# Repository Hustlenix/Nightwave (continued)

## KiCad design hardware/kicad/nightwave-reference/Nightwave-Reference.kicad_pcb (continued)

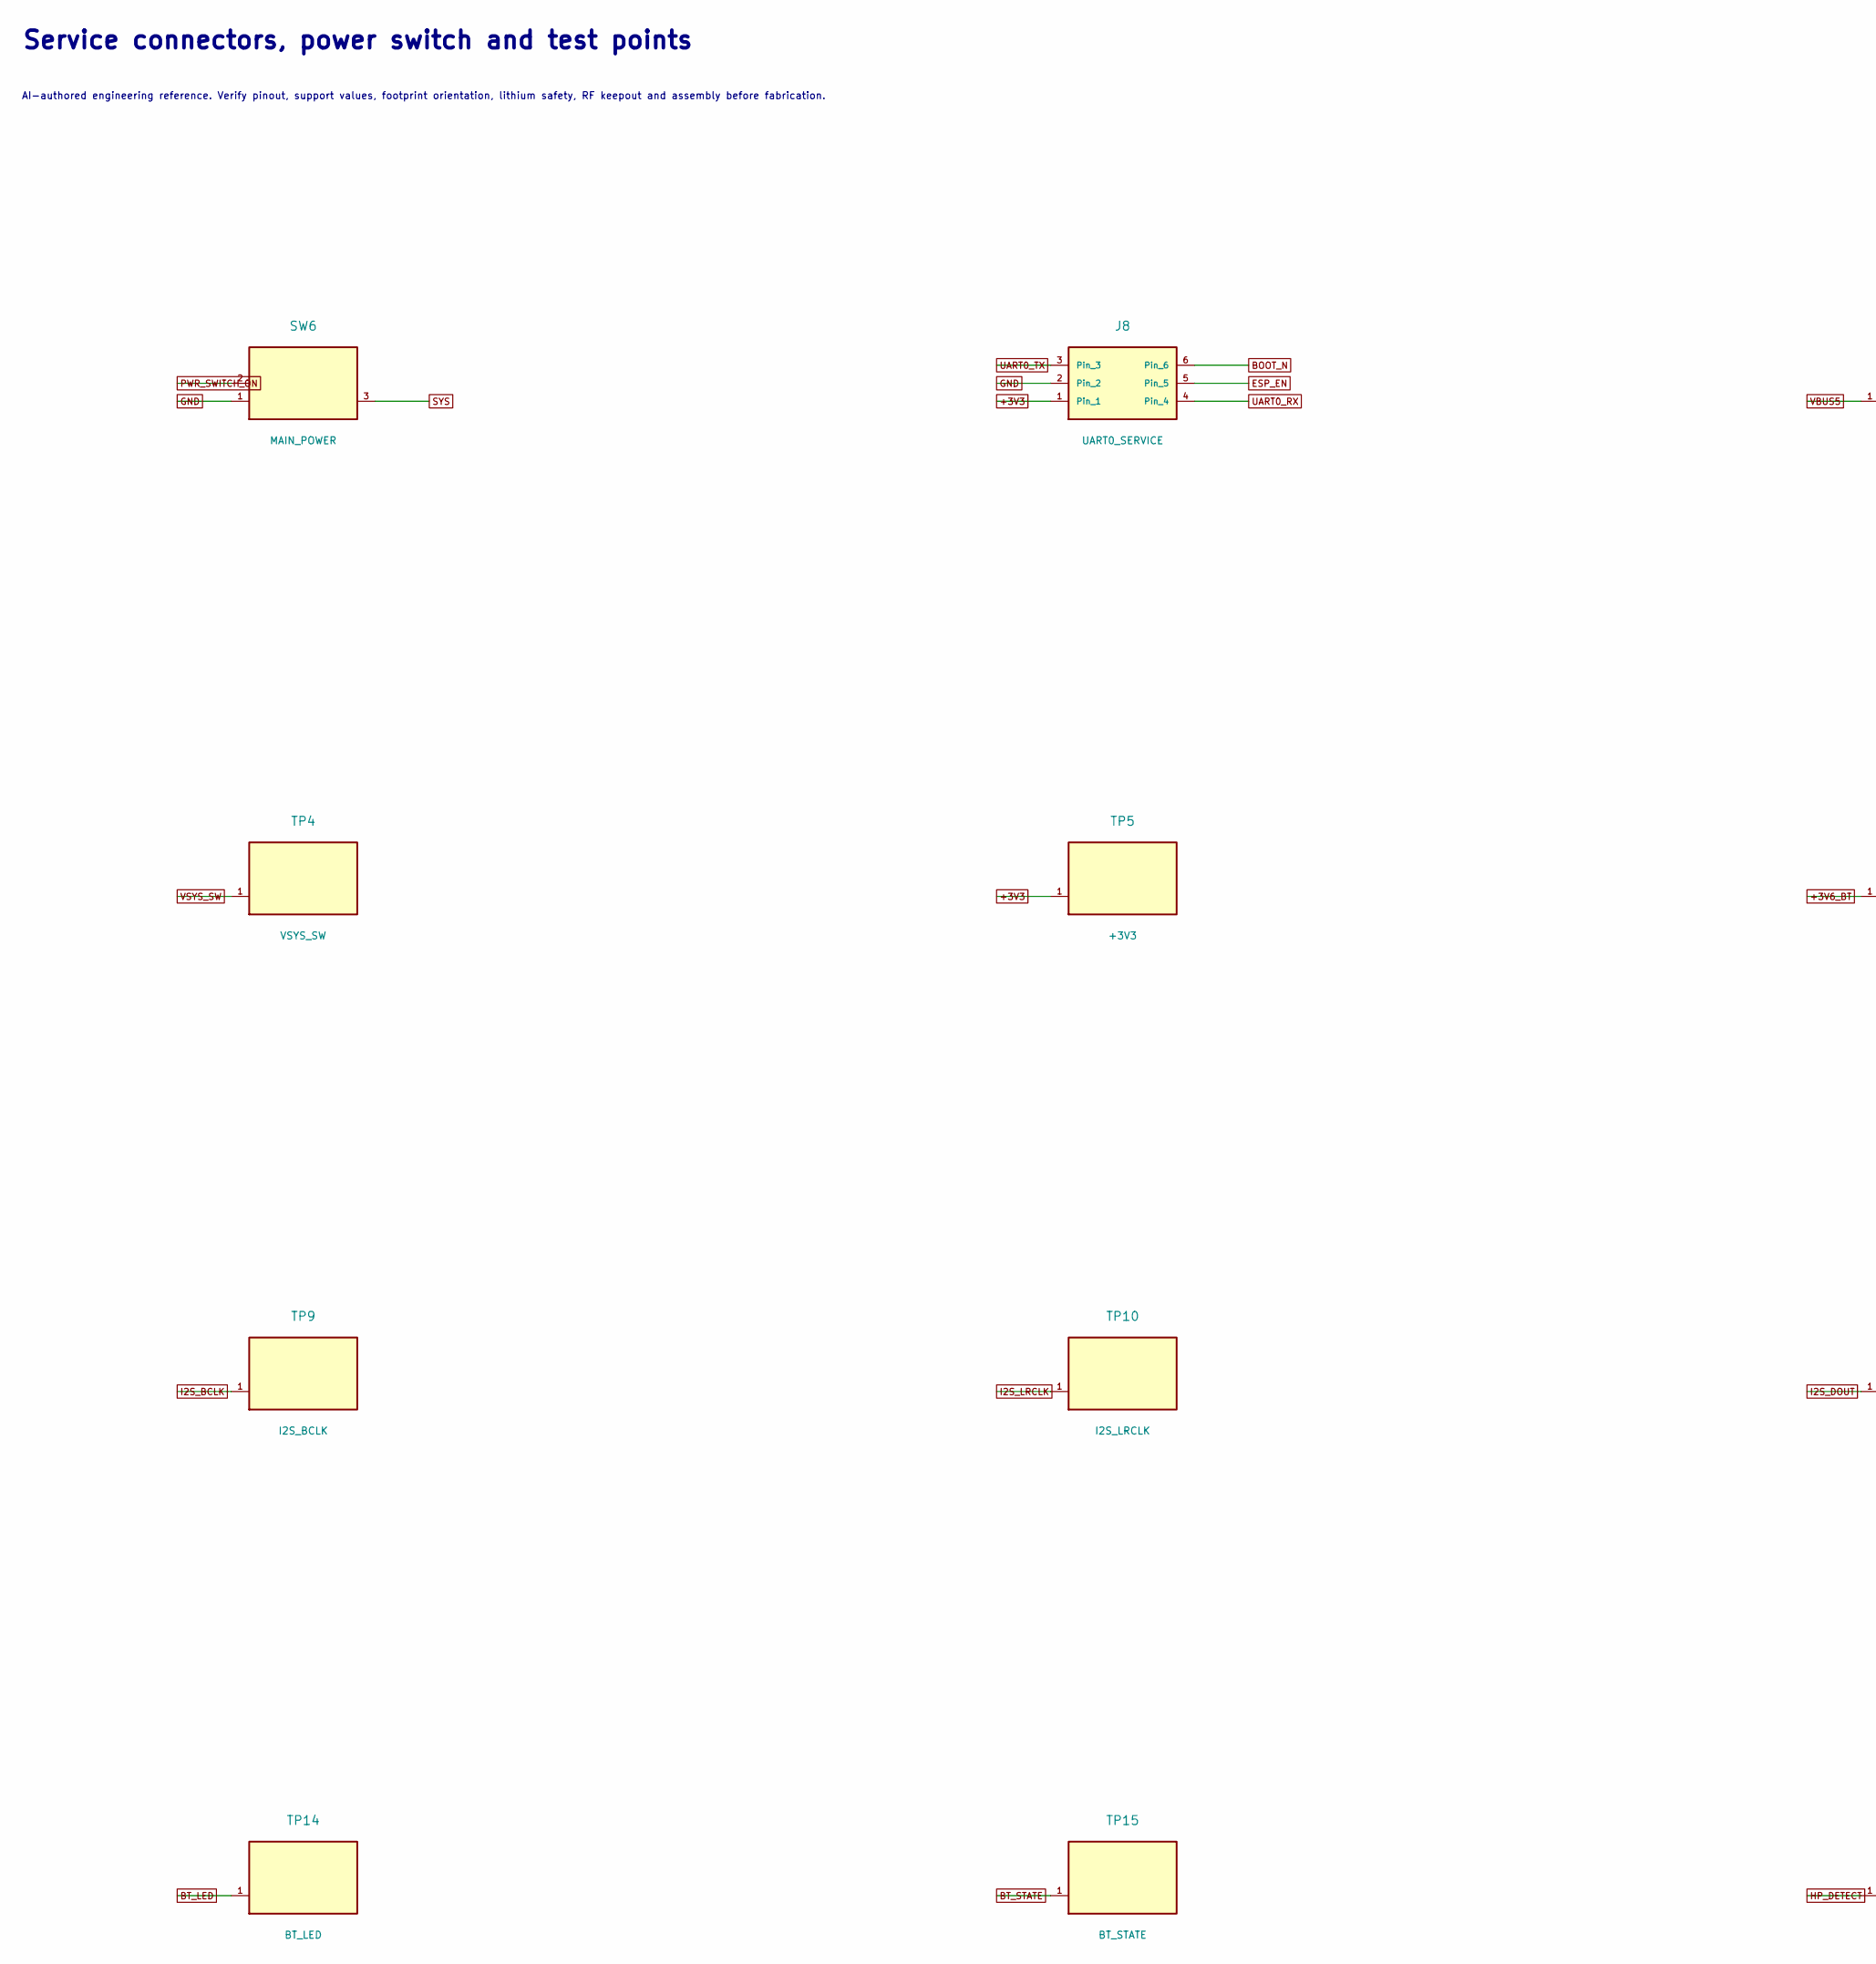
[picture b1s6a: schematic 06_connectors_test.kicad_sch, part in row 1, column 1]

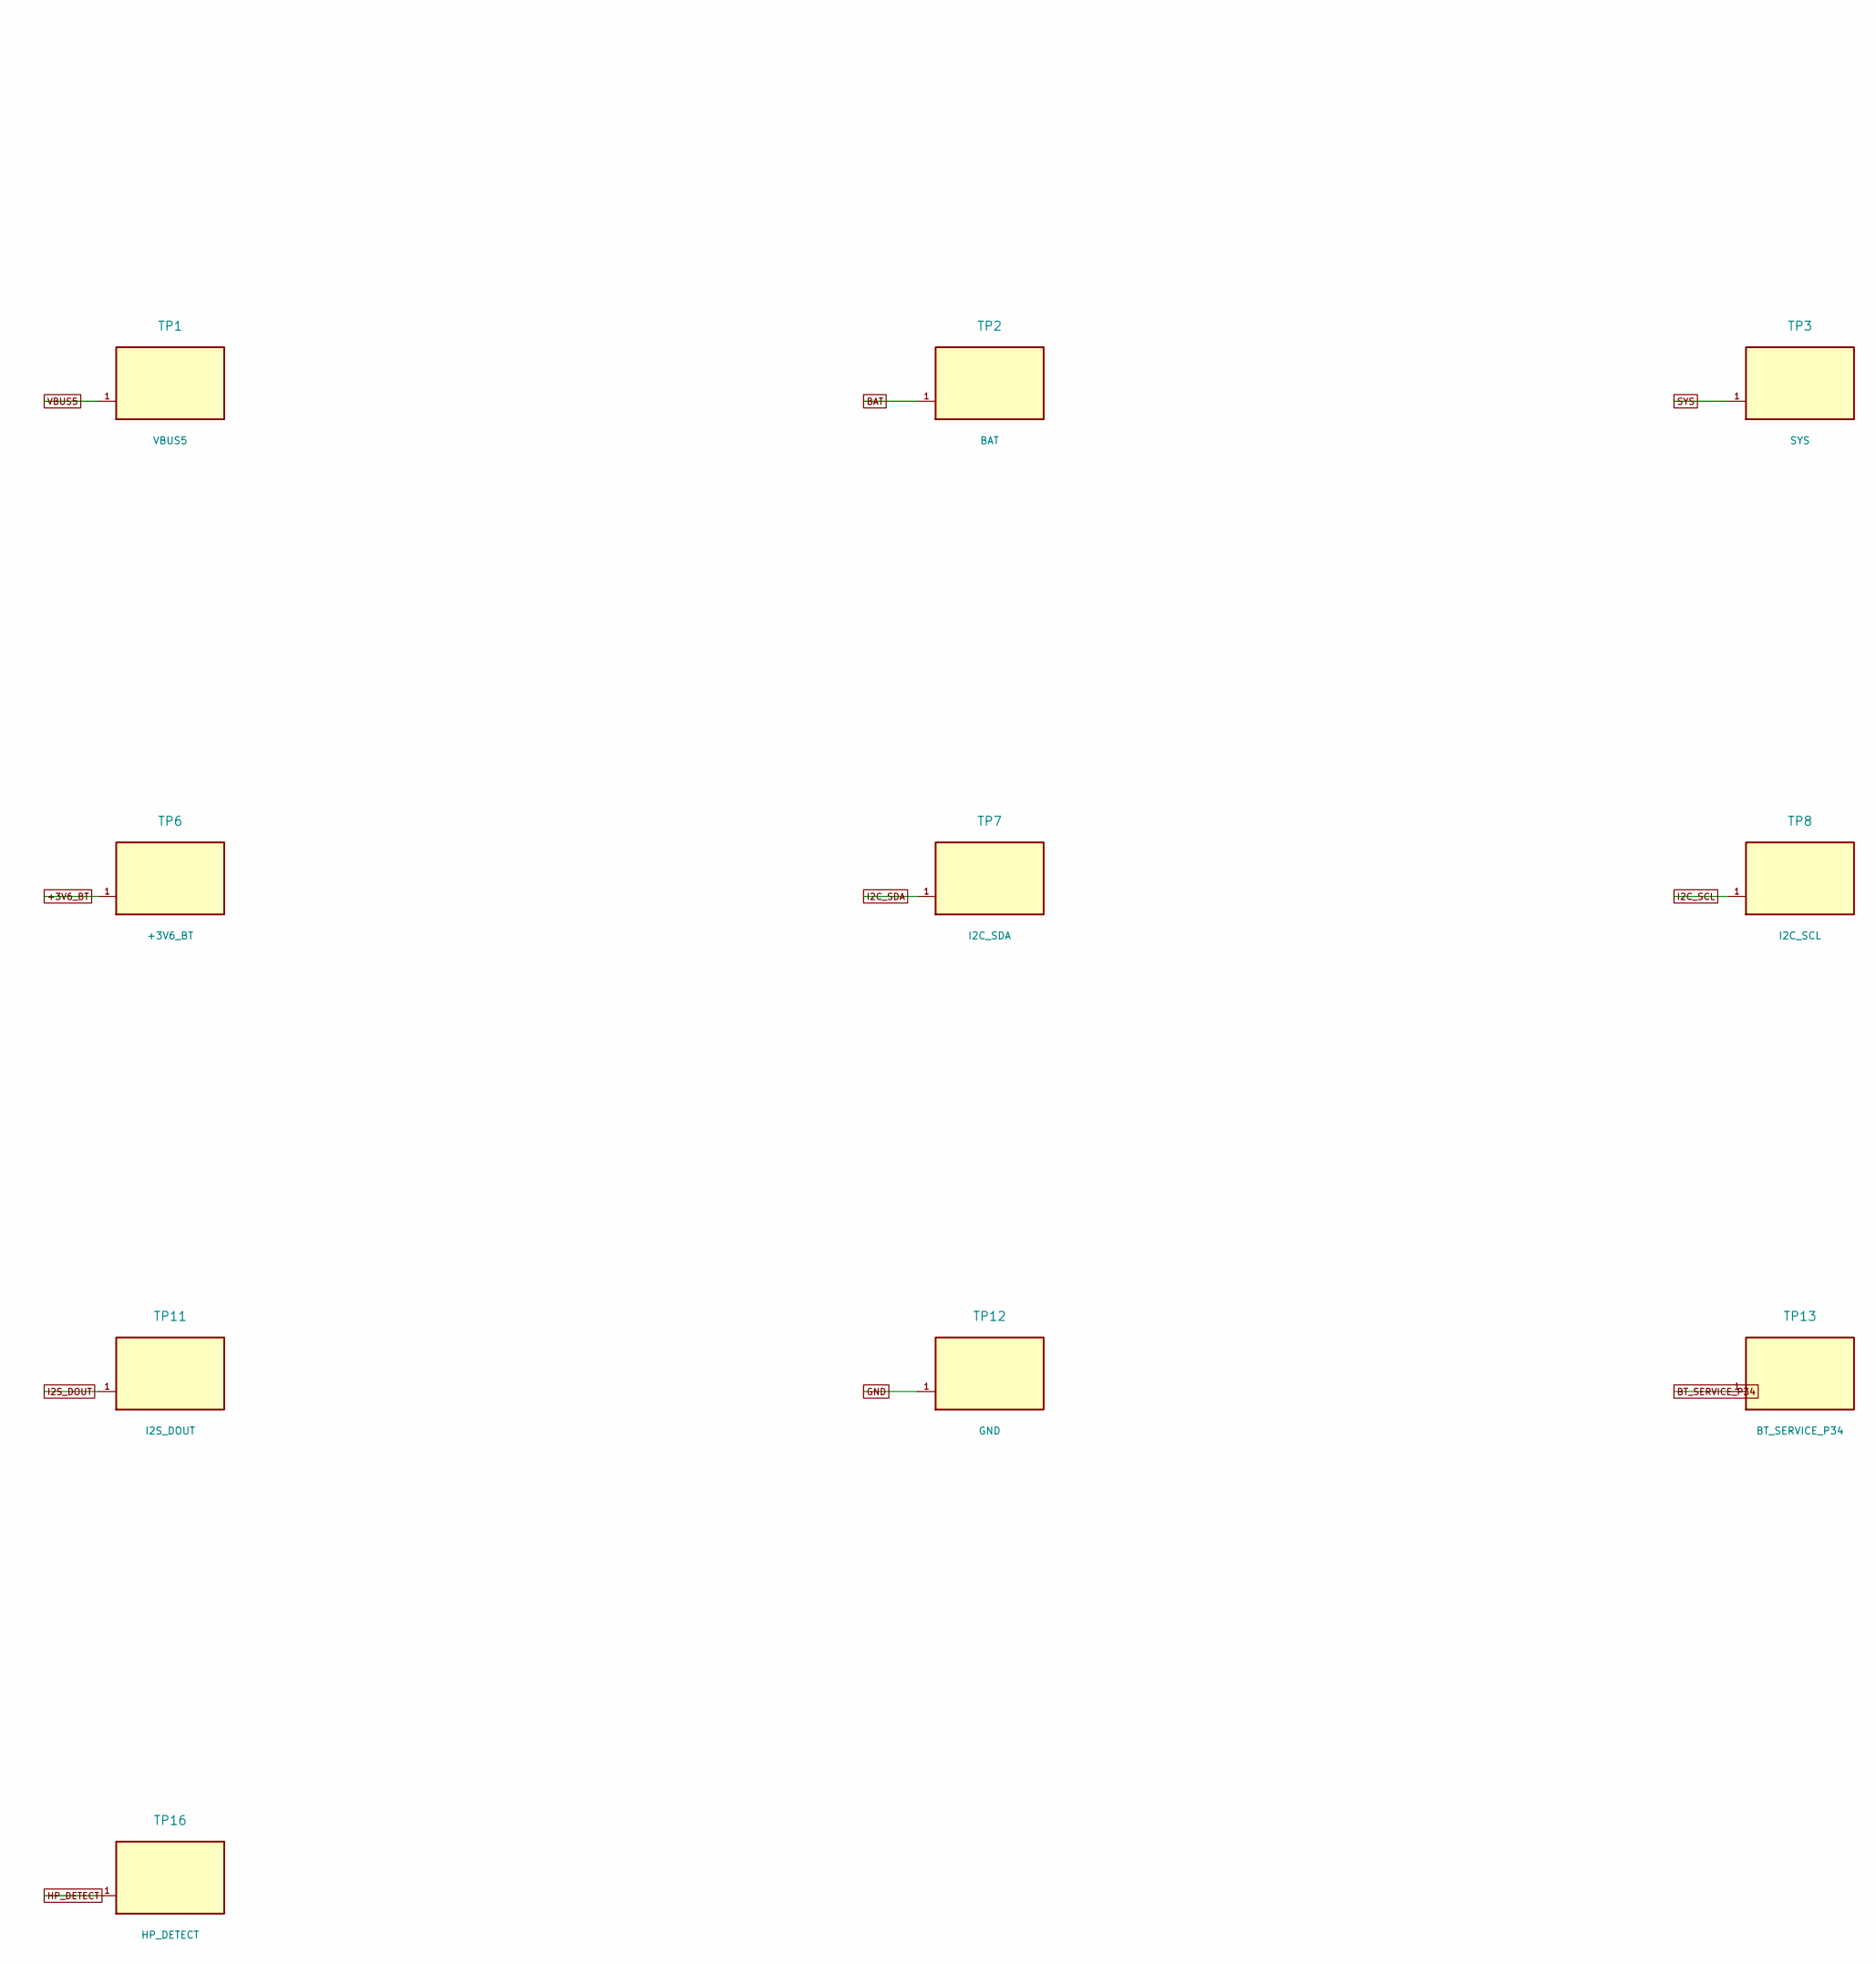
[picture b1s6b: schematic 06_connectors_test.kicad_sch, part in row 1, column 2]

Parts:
J8: UART0_SERVICE; PinHeader_1x06_P2.54mm_Vertical
SW6: MAIN_POWER; SW_SPDT_PCM12
TP1: VBUS5; TestPoint_Pad_D1.0mm
TP2: BAT; TestPoint_Pad_D1.0mm
TP3: SYS; TestPoint_Pad_D1.0mm
TP4: VSYS_SW; TestPoint_Pad_D1.0mm
TP5: +3V3; TestPoint_Pad_D1.0mm
TP6: +3V6_BT; TestPoint_Pad_D1.0mm
TP7: I2C_SDA; TestPoint_Pad_D1.0mm
TP8: I2C_SCL; TestPoint_Pad_D1.0mm
TP9: I2S_BCLK; TestPoint_Pad_D1.0mm
TP10: I2S_LRCLK; TestPoint_Pad_D1.0mm
TP11: I2S_DOUT; TestPoint_Pad_D1.0mm
TP12: GND; TestPoint_Pad_D1.0mm
TP13: BT_SERVICE_P34; TestPoint_Pad_D1.0mm
TP14: BT_LED; TestPoint_Pad_D1.0mm
TP15: BT_STATE; TestPoint_Pad_D1.0mm
TP16: HP_DETECT; TestPoint_Pad_D1.0mm

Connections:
+3V3: J8.1, TP5.1; also elsewhere on the board
+3V6_BT: TP6.1; also elsewhere on the board
BAT: TP2.1; also elsewhere on the board
BOOT_N: J8.6; also elsewhere on the board
BT_LED: TP14.1; also elsewhere on the board
BT_SERVICE_P34: TP13.1; also elsewhere on the board
BT_STATE: TP15.1; also elsewhere on the board
ESP_EN: J8.5; also elsewhere on the board
GND: J8.2, SW6.1 (A), TP12.1; also elsewhere on the board
HP_DETECT: TP16.1; also elsewhere on the board
I2C_SCL: TP8.1; also elsewhere on the board
I2C_SDA: TP7.1; also elsewhere on the board
I2S_BCLK: TP9.1; also elsewhere on the board
I2S_DOUT: TP11.1; also elsewhere on the board
I2S_LRCLK: TP10.1; also elsewhere on the board
PWR_SWITCH_ON: SW6.2 (B); also elsewhere on the board
SYS: SW6.3 (C), TP3.1; also elsewhere on the board
UART0_RX: J8.4; also elsewhere on the board
UART0_TX: J8.3; also elsewhere on the board
VBUS5: TP1.1; also elsewhere on the board
VSYS_SW: TP4.1; also elsewhere on the board

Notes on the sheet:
Service connectors, power switch and test points
AI-authored engineering reference. Verify pinout, support values, footprint orientation, lithium safety, RF keepout and assembly before fabrication.

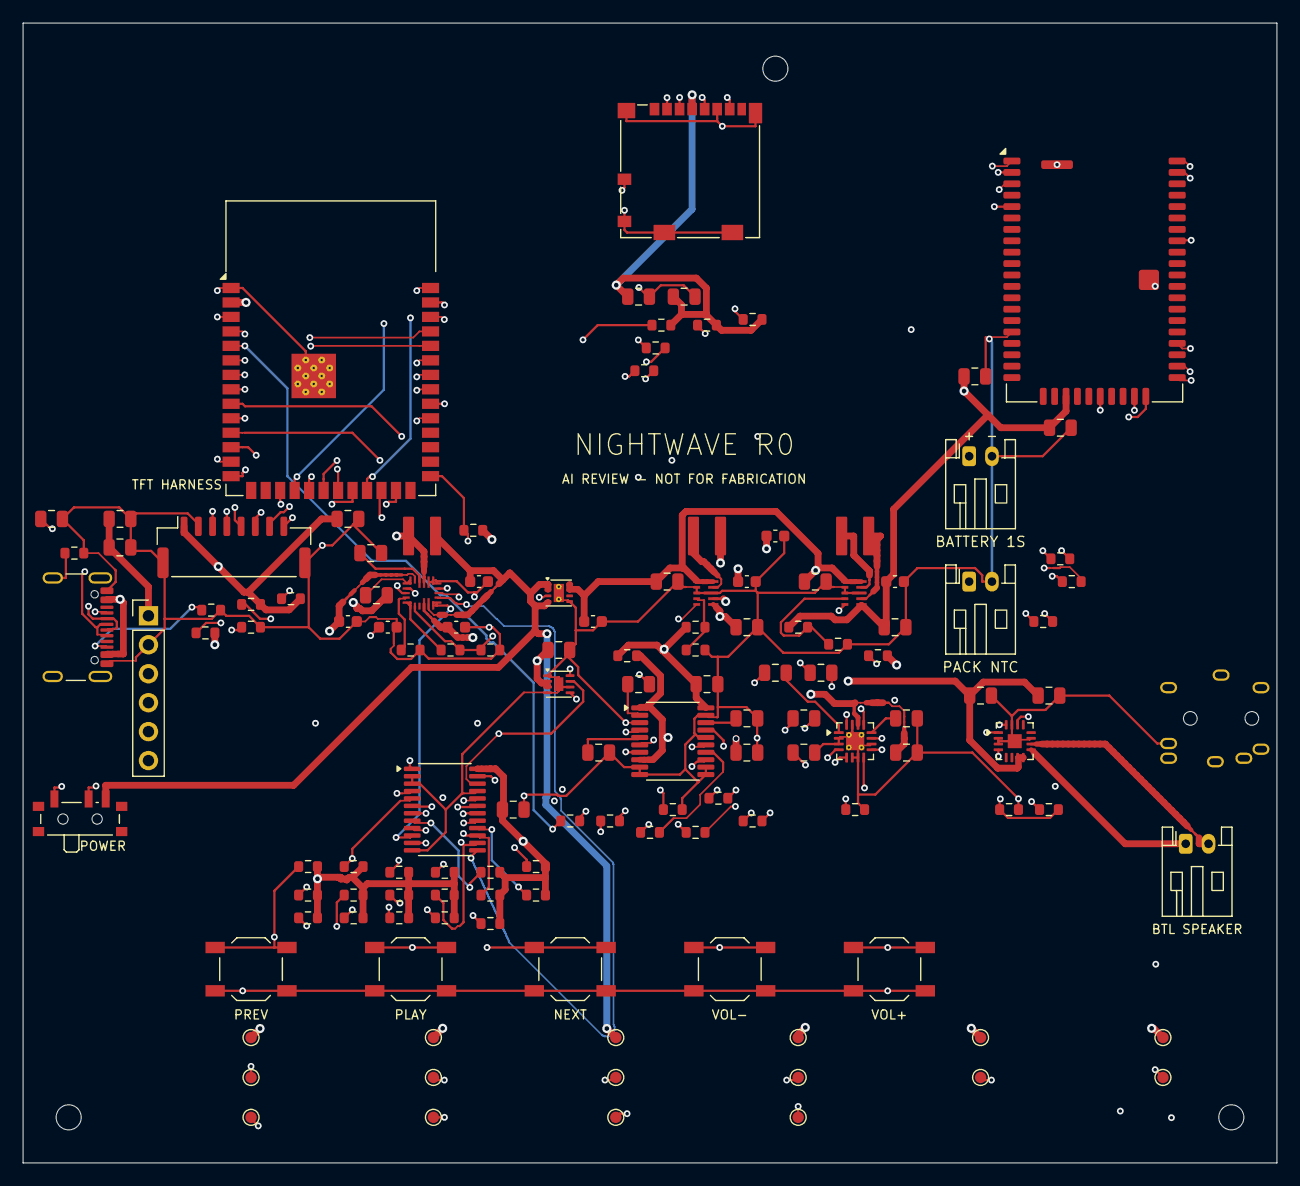
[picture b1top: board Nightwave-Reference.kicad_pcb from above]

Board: 4 copper layers, 110.0 x 100.0 mm, 135 parts (0 on the bottom side), 104 nets.

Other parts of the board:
H1, H2, H3: M2_NPTH_NYLON_HARDWARE; MountingHole_2.2mm_M2

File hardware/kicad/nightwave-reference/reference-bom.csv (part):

Reference,Qty,Manufacturer,MPN,Value,Footprint,Datasheet,Unit_Price_USD,Supplier_URL,Status
J1,1,GCT,USB4105-GF-A,USB4105-GF-A,Connector_USB:USB_C_Receptacle_GCT_USB4105-xx-A_16P_TopMnt_Horizontal,https://gct.co/files/specs/usb4105-spec.pdf,,,REFERENCE_REVIEW_REQUIRED
U3,1,Texas Instruments,BQ25628ERYKR,BQ25628ERYKR,Nightwave:TI_RYK0018A,https://www.ti.com/lit/ds/symlink/bq25628e.pdf,,,REFERENCE_REVIEW_REQUIRED
U4,1,Texas Instruments,TPS22965DSGR,TPS22965DSGR,Package_SON:Texas_DSG0008A_WSON-8-1EP_2x2mm_P0.5mm_EP0.9x1.6mm_ThermalVias,https://www.ti.com/lit/ds/symlink/tps22965.pdf,,,REFERENCE_REVIEW_REQUIRED
U5,1,Texas Instruments,TPS63802DLAR,TPS63802DLAR,Nightwave:TI_DLA0010A,https://www.ti.com/lit/ds/symlink/tps63802.pdf,,,REFERENCE_REVIEW_REQUIRED
U6,1,Texas Instruments,TPS63802DLAR,TPS63802DLAR,Nightwave:TI_DLA0010A,https://www.ti.com/lit/ds/symlink/tps63802.pdf,,,REFERENCE_REVIEW_REQUIRED
U7,1,Analog Devices,MAX17048G+T10,MAX17048G+T10,Package_DFN_QFN:TDFN-8-1EP_2x2mm_P0.5mm_EP0.8x1.2mm,https://www.analog.com/media/en/technical-documentation/data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,,,REFERENCE_REVIEW_REQUIRED
J2,1,JST,S2B-PH-K-S,BATTERY_CONNECTOR,Connector_JST:JST_PH_S2B-PH-K_1x02_P2.00mm_Horizontal,https://www.jst-mfg.com/product/pdf/eng/ePH.pdf,,,REFERENCE_REVIEW_REQUIRED
J3,1,JST,S2B-PH-K-S,EXTERNAL_10K_NTC,Connector_JST:JST_PH_S2B-PH-K_1x02_P2.00mm_Horizontal,https://www.jst-mfg.com/product/pdf/eng/ePH.pdf,,,REFERENCE_REVIEW_REQUIRED
U1,1,Espressif Systems,ESP32-S3-WROOM-1-N16R8,ESP32-S3-WROOM-1-N16R8,RF_Module:ESP32-S3-WROOM-1,https://www.espressif.com/sites/default/files/documentation/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,6.76,,REFERENCE_REVIEW_REQUIRED
J4,1,Molex,104031-0811,Molex 104031-0811,Connector_Card:microSD_HC_Molex_104031-0811,https://www.molex.com/en-us/products/part-detail/1040310811,2.21,,REFERENCE_REVIEW_REQUIRED
U8,1,Texas Instruments,PCM5102APWR,PCM5102APWR,Package_SO:Texas_PW0020A_TSSOP-20_4.4x6.5mm_P0.65mm,https://www.ti.com/lit/ds/symlink/pcm5102a.pdf,4.04,,REFERENCE_REVIEW_REQUIRED
U9,1,Texas Instruments,TPA6132A2RTER,TPA6132A2RTER,Package_DFN_QFN:VQFN-16-1EP_3x3mm_P0.5mm_EP1.6x1.6mm_ThermalVias,https://www.ti.com/lit/ds/symlink/tpa6132a2.pdf,1.10,,REFERENCE_REVIEW_REQUIRED
U10,1,Analog Devices,MAX98357AETE+T,MAX98357AETE+T,Package_DFN_QFN:TQFN-16-1EP_3x3mm_P0.5mm_EP1.23x1.23mm,https://www.analog.com/media/en/technical-documentation/data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,,,REFERENCE_REVIEW_REQUIRED
J5,1,Same Sky,SJ3-350153AG-TR,SJ3-350153AG-TR,Nightwave:SameSky_SJ3-350153AG,https://www.sameskydevices.com/product/resource/sj3-35015x.pdf,,,REFERENCE_REVIEW_REQUIRED
J6,1,JST,S2B-PH-K-S,BTL_SPEAKER_CONNECTOR,Connector_JST:JST_PH_S2B-PH-K_1x02_P2.00mm_Horizontal,https://www.jst-mfg.com/product/pdf/eng/ePH.pdf,,,REFERENCE_REVIEW_REQUIRED
U11,1,Texas Instruments,TCA9535PWR,TCA9535PWR,Package_SO:TSSOP-24_4.4x7.8mm_P0.65mm,https://www.ti.com/lit/ds/symlink/tca9535.pdf,,,REFERENCE_REVIEW_REQUIRED
J7,1,JST,SM08B-GHS-TB(LF)(SN),TFT_24382_HARNESS,Connector_JST:JST_GH_SM08B-GHS-TB_1x08-1MP_P1.25mm_Horizontal,https://www.jst-mfg.com/product/pdf/eng/eGH.pdf,,,REFERENCE_REVIEW_REQUIRED
SW1,1,,PENDING_SELECTION,PREV,Button_Switch_SMD:SW_SPST_TL3342,,,,MPN_PENDING_SELECTION
SW2,1,,PENDING_SELECTION,PLAY_PAUSE,Button_Switch_SMD:SW_SPST_TL3342,,,,MPN_PENDING_SELECTION
SW3,1,,PENDING_SELECTION,NEXT,Button_Switch_SMD:SW_SPST_TL3342,,,,MPN_PENDING_SELECTION
SW4,1,,PENDING_SELECTION,VOL_DOWN,Button_Switch_SMD:SW_SPST_TL3342,,,,MPN_PENDING_SELECTION
SW5,1,,PENDING_SELECTION,VOL_UP,Button_Switch_SMD:SW_SPST_TL3342,,,,MPN_PENDING_SELECTION
U12,1,Microchip Technology,BM83SM1-00TA,BM83SM1-00TA,Nightwave:Microchip_BM83_GroundLands,https://ww1.microchip.com/downloads/en/DeviceDoc/BM83-Blueto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,12.20,,REFERENCE_REVIEW_REQUIRED
SW6,1,,PENDING_SELECTION,MAIN_POWER,Button_Switch_SMD:SW_SPDT_PCM12,,,,MPN_PENDING_SELECTION
J8,1,,PENDING_SELECTION,UART0_SERVICE,Connector_PinHeader_2.54mm:PinHeader_1x06_P2.54mm_Vertical,,,,MPN_PENDING_SELECTION
TP1,1,,NO_PURCHASE,VBUS5,TestPoint:TestPoint_Pad_D1.0mm,,,,PCB_FEATURE
TP2,1,,NO_PURCHASE,BAT,TestPoint:TestPoint_Pad_D1.0mm,,,,PCB_FEATURE
TP3,1,,NO_PURCHASE,SYS,TestPoint:TestPoint_Pad_D1.0mm,,,,PCB_FEATURE
TP4,1,,NO_PURCHASE,VSYS_SW,TestPoint:TestPoint_Pad_D1.0mm,,,,PCB_FEATURE
TP5,1,,NO_PURCHASE,+3V3,TestPoint:TestPoint_Pad_D1.0mm,,,,PCB_FEATURE
TP6,1,,NO_PURCHASE,+3V6_BT,TestPoint:TestPoint_Pad_D1.0mm,,,,PCB_FEATURE
TP7,1,,NO_PURCHASE,I2C_SDA,TestPoint:TestPoint_Pad_D1.0mm,,,,PCB_FEATURE
TP8,1,,NO_PURCHASE,I2C_SCL,TestPoint:TestPoint_Pad_D1.0mm,,,,PCB_FEATURE
TP9,1,,NO_PURCHASE,I2S_BCLK,TestPoint:TestPoint_Pad_D1.0mm,,,,PCB_FEATURE
TP10,1,,NO_PURCHASE,I2S_LRCLK,TestPoint:TestPoint_Pad_D1.0mm,,,,PCB_FEATURE
TP11,1,,NO_PURCHASE,I2S_DOUT,TestPoint:TestPoint_Pad_D1.0mm,,,,PCB_FEATURE
TP12,1,,NO_PURCHASE,GND,TestPoint:TestPoint_Pad_D1.0mm,,,,PCB_FEATURE
TP13,1,,NO_PURCHASE,BT_SERVICE_P34,TestPoint:TestPoint_Pad_D1.0mm,,,,PCB_FEATURE
TP14,1,,NO_PURCHASE,BT_LED,TestPoint:TestPoint_Pad_D1.0mm,,,,PCB_FEATURE
TP15,1,,NO_PURCHASE,BT_STATE,TestPoint:TestPoint_Pad_D1.0mm,,,,PCB_FEATURE
TP16,1,,NO_PURCHASE,HP_DETECT,TestPoint:TestPoint_Pad_D1.0mm,,,,PCB_FEATURE
R1,1,,PENDING_SELECTION,5.1k,Resistor_SMD:R_0603_1608Metric,,,,MPN_PENDING_SELECTION
R2,1,,PENDING_SELECTION,5.1k,Resistor_SMD:R_0603_1608Metric,,,,MPN_PENDING_SELECTION
R3,1,,PENDING_SELECTION,4.7k,Resistor_SMD:R_0603_1608Metric,,,,MPN_PENDING_SELECTION
R4,1,,PENDING_SELECTION,4.7k,Resistor_SMD:R_0603_1608Metric,,,,MPN_PENDING_SELECTION
R5,1,,PENDING_SELECTION,22,Resistor_SMD:R_0603_1608Metric,,,,MPN_PENDING_SELECTION
R6,1,,PENDING_SELECTION,22,Resistor_SMD:R_0603_1608Metric,,,,MPN_PENDING_SELECTION
R7,1,,PENDING_SELECTION,33,Resistor_SMD:R_0603_1608Metric,,,,MPN_PENDING_SELECTION
R8,1,,PENDING_SELECTION,33,Resistor_SMD:R_0603_1608Metric,,,,MPN_PENDING_SELECTION
R9,1,,PENDING_SELECTION,33,Resistor_SMD:R_0603_1608Metric,,,,MPN_PENDING_SELECTION
R10,1,,PENDING_SELECTION,33,Resistor_SMD:R_0603_1608Metric,,,,MPN_PENDING_SELECTION
R11,1,,PENDING_SELECTION,33,Resistor_SMD:R_0603_1608Metric,,,,MPN_PENDING_SELECTION
R12,1,,PENDING_SELECTION,33,Resistor_SMD:R_0603_1608Metric,,,,MPN_PENDING_SELECTION
R13,1,,PENDING_SELECTION,33,Resistor_SMD:R_0603_1608Metric,,,,MPN_PENDING_SELECTION
R14,1,,PENDING_SELECTION,33,Resistor_SMD:R_0603_1608Metric,,,,MPN_PENDING_SELECTION
R15,1,,PENDING_SELECTION,33,Resistor_SMD:R_0603_1608Metric,,,,MPN_PENDING_SELECTION
C1,1,,PENDING_SELECTION,10u,Capacitor_SMD:C_0603_1608Metric,,,,MPN_PENDING_SELECTION
C2,1,,PENDING_SELECTION,10u,Capacitor_SMD:C_0603_1608Metric,,,,MPN_PENDING_SELECTION
C3,1,,PENDING_SELECTION,22u,Capacitor_SMD:C_0603_1608Metric,,,,MPN_PENDING_SELECTION
C4,1,,PENDING_SELECTION,22u,Capacitor_SMD:C_0603_1608Metric,,,,MPN_PENDING_SELECTION
C5,1,,PENDING_SELECTION,22u,Capacitor_SMD:C_0603_1608Metric,,,,MPN_PENDING_SELECTION
C6,1,,PENDING_SELECTION,22u,Capacitor_SMD:C_0603_1608Metric,,,,MPN_PENDING_SELECTION
C7,1,,PENDING_SELECTION,10u,Capacitor_SMD:C_0603_1608Metric,,,,MPN_PENDING_SELECTION
C8,1,,PENDING_SELECTION,4.7u,Capacitor_SMD:C_0603_1608Metric,,,,MPN_PENDING_SELECTION
L1,1,Coilcraft,XFL4015-471MEC,0.47uH XFL4015-471MEC,Nightwave:Coilcraft_XFL4015,https://www.coilcraft.com/getmedia/84927b8b-f089-421b-a7f4-a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,,,REFERENCE_REVIEW_REQUIRED
L2,1,Coilcraft,XFL4015-471MEC,0.47uH XFL4015-471MEC,Nightwave:Coilcraft_XFL4015,https://www.coilcraft.com/getmedia/84927b8b-f089-421b-a7f4-a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,,,REFERENCE_REVIEW_REQUIRED
L3,1,Coilcraft,XFL4015-701MEC,0.7uH XFL4015-701MEC,Nightwave:Coilcraft_XFL4015,https://www.coilcraft.com/getmedia/84927b8b-f089-421b-a7f4-a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,,,REFERENCE_REVIEW_REQUIRED
R16,1,,PENDING_SELECTION,511k,Resistor_SMD:R_0603_1608Metric,,,,MPN_PENDING_SELECTION
R17,1,,PENDING_SELECTION,91k,Resistor_SMD:R_0603_1608Metric,,,,MPN_PENDING_SELECTION
R18,1,,PENDING_SELECTION,562k,Resistor_SMD:R_0603_1608Metric,,,,MPN_PENDING_SELECTION
R19,1,,PENDING_SELECTION,91k,Resistor_SMD:R_0603_1608Metric,,,,MPN_PENDING_SELECTION
R20,1,,PENDING_SELECTION,5.49k,Resistor_SMD:R_0603_1608Metric,,,,MPN_PENDING_SELECTION
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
